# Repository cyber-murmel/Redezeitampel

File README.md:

# Redezeitampel
A traffic light like device to keep discussions calm and ordered

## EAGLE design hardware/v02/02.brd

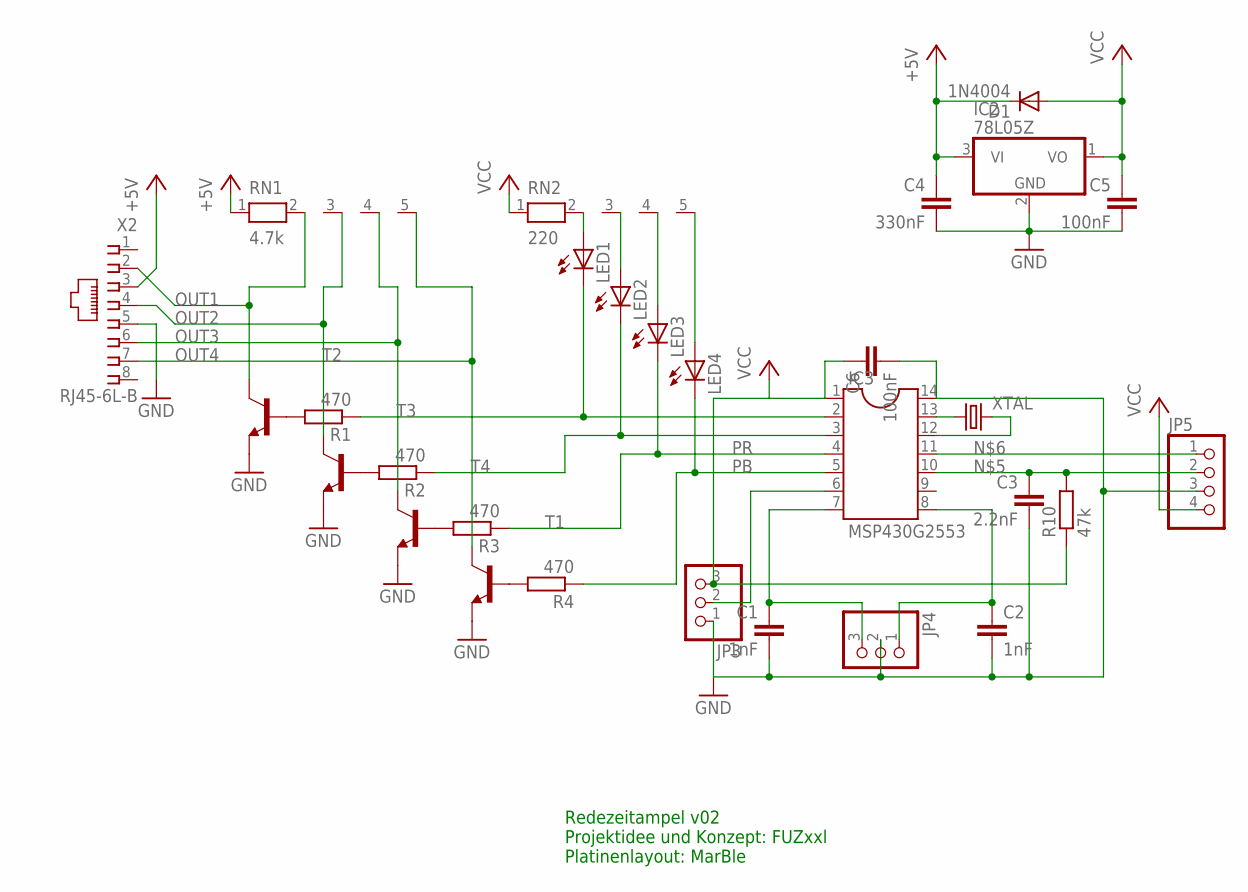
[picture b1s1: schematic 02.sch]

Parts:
C1, C2: 1nF; C025-024X044
C3: 2.2nF; C025-024X044
C4: 330nF; C050-024X044
C5, C6: 100nF; C050-024X044
D1: 1N4004; DO41-10
IC2: 78L05Z; TO92
IC3: MSP430G2553; SOCKET-14
JP3, JP4: PINHD-1X3; 1X03
JP5: PINHD-1X4; 1X04
LED1, LED2, LED3, LED4: LED5MM
R1, R2, R3, R4: 470; 0207/12
R10: 47k; 0207/7
RN1: 4.7k; RN-5
RN2: 220; RN-5
T1, T2, T3, T4: -NPN-TO92-EBC; TO92-EBC
X2: RJ45-6L-B; RJ45-NO-SHIELD
XTAL: CRYSTALTC26H; TC26H

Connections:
+5V: C4.1, D1.C, IC2.3 (VI), RN1.1, X2.3
GND: C1.2, C2.2, C3.2, C4.2, C5.2, C6.2, IC2.2 (GND), IC3.14, JP3.1, JP4.2, JP5.3, T1.E, T2.E, T3.E, T4.E, X2.5
unnamed: IC3.6, JP3.2
unnamed: IC3.13, XTAL.1
unnamed: C1.1, IC3.7, JP4.3
unnamed: C2.1, IC3.8, JP4.1
unnamed: C3.1, IC3.10, JP5.2, R10.2
unnamed: IC3.11, JP5.1
unnamed: IC3.12, XTAL.2
unnamed: LED1.A, RN2.2
unnamed: IC3.3, LED2.K (C), R2.1
unnamed: LED2.A, RN2.3
unnamed: R4.2, T1.B
unnamed: IC3.2, LED1.K (C), R1.1
unnamed: LED3.A, RN2.4
unnamed: LED4.A, RN2.5
unnamed: R1.2, T2.B
unnamed: R2.2, T3.B
unnamed: R3.2, T4.B
OUT1: RN1.2, T2.C, X2.2
OUT2: RN1.3, T3.C, X2.4
OUT3: RN1.4, T4.C, X2.6
OUT4: RN1.5, T1.C, X2.7
PB: IC3.5, LED4.K (C), R4.1
PR: IC3.4, LED3.K (C), R3.1
VCC: C5.1, C6.1, D1.A, IC2.1 (VO), IC3.1, JP3.3, JP5.4, R10.1, RN2.1

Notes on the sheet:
Redezeitampel v02 Projektidee und Konzept: FUZxxl Platinenlayout: MarBle

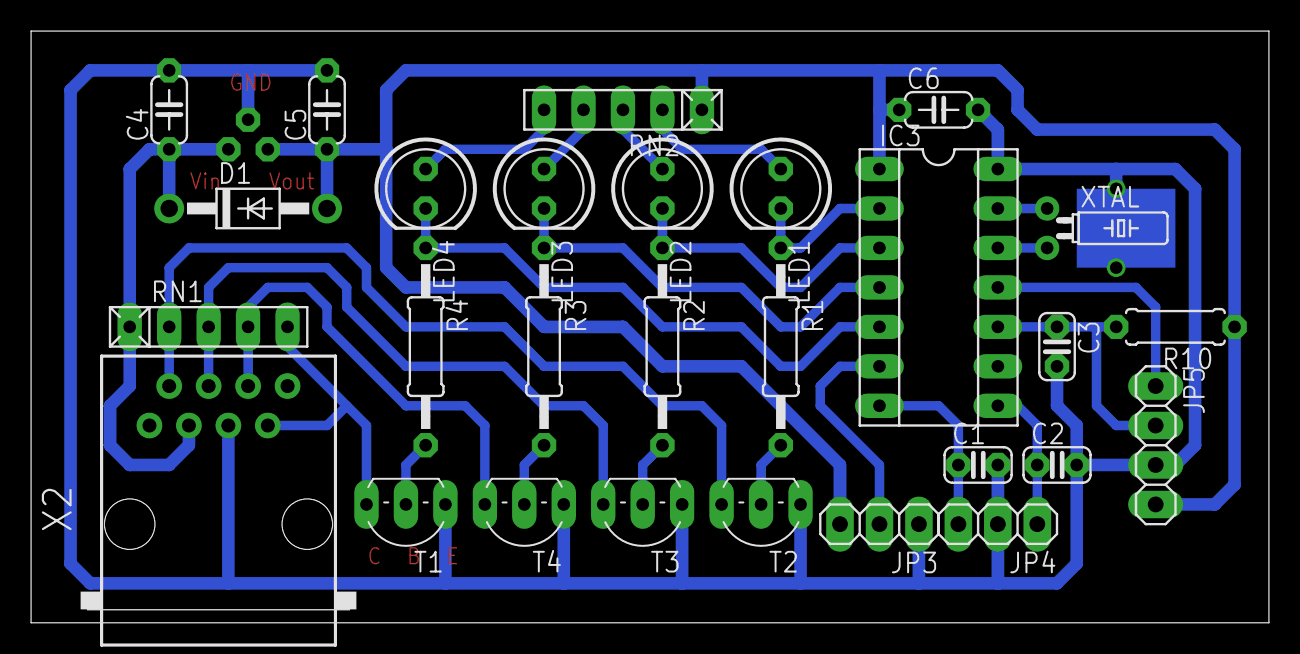
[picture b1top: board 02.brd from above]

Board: 2 copper layers, 79.7 x 38.1 mm, 29 parts (1 on the bottom side), 26 nets.

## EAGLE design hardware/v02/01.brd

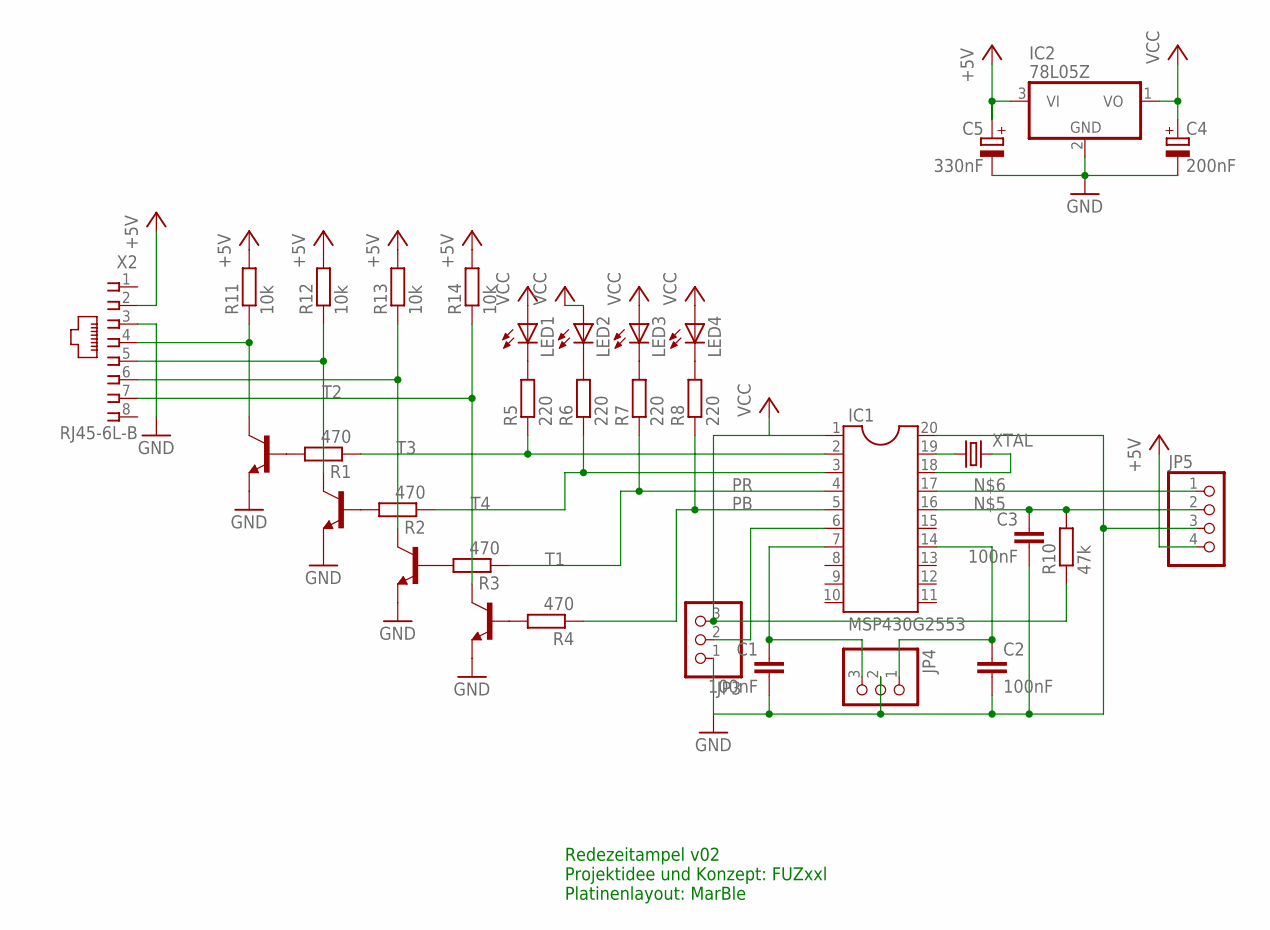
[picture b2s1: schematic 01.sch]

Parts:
C1, C2, C3: 100nF; C025-024X044
C4: 200nF; B45181A
C5: 330nF; B45181A
IC1: MSP430G2553; DIL20
IC2: 78L05Z; TO92
JP3, JP4: PINHD-1X3; 1X03
JP5: PINHD-1X4/90; 1X04/90
LED1, LED2, LED3, LED4: LED5MM
R1, R2, R3, R4: 470; 0207/10
R5, R6, R7, R8: 220; 0207/10
R10: 47k; 0207/10
R11, R12, R13, R14: 10k; 0207/10
T1, T2, T3, T4: -NPN-TO92-EBC; TO92-EBC
X2: RJ45-6L-B; RJ45-NO-SHIELD
XTAL: CRYSTALTC26H; TC26H

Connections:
+5V: C5.+, IC2.3 (VI), JP5.4, R11.2, R12.2, R13.2, R14.2, X2.2
GND: C1.2, C2.2, C3.2, C4.-, C5.-, IC1.20, IC2.2 (GND), JP3.1, JP4.2, JP5.3, T1.E, T2.E, T3.E, T4.E, X2.3
unnamed: IC1.6, JP3.2
unnamed: IC1.19, XTAL.1
unnamed: C1.1, IC1.7, JP4.3
unnamed: C2.1, IC1.14, JP4.1
unnamed: C3.1, IC1.16, JP5.2, R10.2
unnamed: IC1.17, JP5.1
unnamed: IC1.18, XTAL.2
unnamed: LED4.K (C), R8.2
unnamed: IC1.3, R2.1, R6.1
unnamed: R4.2, T1.B
unnamed: IC1.2, R1.1, R5.1
unnamed: LED1.K (C), R5.2
unnamed: R1.2, T2.B
unnamed: LED2.K (C), R6.2
unnamed: R2.2, T3.B
unnamed: LED3.K (C), R7.2
unnamed: R3.2, T4.B
unnamed: R14.1, T1.C, X2.7
unnamed: R13.1, T4.C, X2.6
unnamed: R12.1, T3.C, X2.5
unnamed: R11.1, T2.C, X2.4
PB: IC1.5, R4.1, R8.1
PR: IC1.4, R3.1, R7.1
VCC: C4.+, IC1.1, IC2.1 (VO), JP3.3, LED1.A, LED2.A, LED3.A, LED4.A, R10.1

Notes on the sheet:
Redezeitampel v02 Projektidee und Konzept: FUZxxl Platinenlayout: MarBle

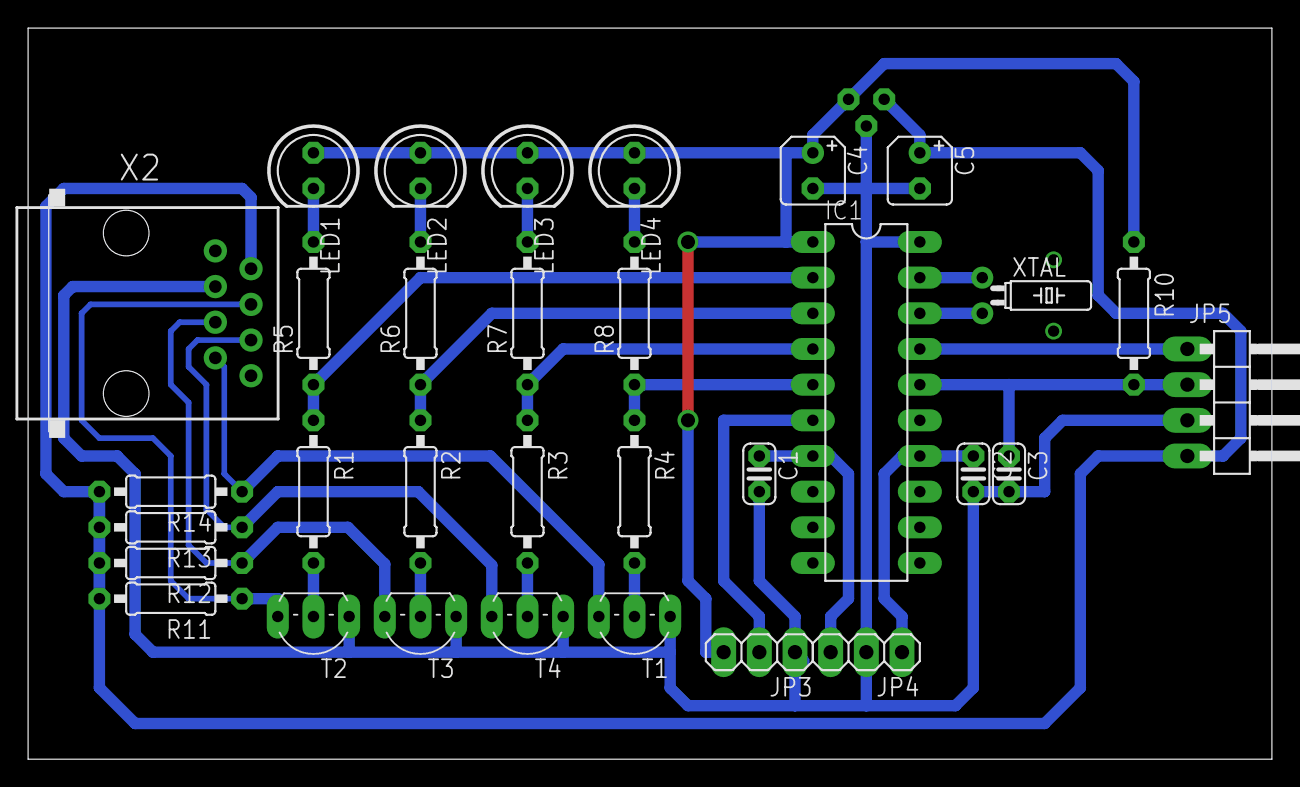
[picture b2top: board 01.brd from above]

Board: 2 copper layers, 88.6 x 52.0 mm, 33 parts (1 on the bottom side), 26 nets.

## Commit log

2015-10-06 Schaltplan der Steuerplatine
2015-10-06 kleine Korrekturen am Schaltplan
2015-10-08 mal gucken, was mit symlinks passiert
2015-10-08 deleted symlink
2015-10-08 Added eagle files
    old eagle files in v01
    at the moment v02 is copy of v01
2015-10-08 XTAl flat on board; holes for additional wire
2015-10-08 C3 between RST and GND
2015-10-08 C4 between Vcc and GND
2015-10-08 rearranged transistorsand LEDs; additional resistors; pre final version
2015-10-08 add pictures
2015-10-08 remove unneccesary files
2015-10-08 Reverting to the state of the project at 678c016824e7177dd6d43b6df3310d67c5eb1f45
2015-10-08 remove/rename some files
2015-10-09 avoid one wire bridge
2015-10-09 wire labels
2015-10-09 Layout der 4. Revision als Skizze
2015-10-09 Entwicklungszustand der Firmware
2015-10-09 winzige Korrektur des Schaltplans
2015-10-09 Besserer Dateiname für layout.jpg
2015-10-09 resistor networks, reposition Vreg
2015-10-09 images of newest version
2015-10-09 rearrange
2015-10-09 Datenblätter
2015-10-09 smaller IC; rearrange
2015-10-09 remove old files
2015-10-09 minor change
2015-10-09 denser distribution
2015-10-09 all caps converted to ceramic; diode over Vreg
2015-10-09 reposition XTAL
2015-10-09 minor changes
2015-10-09 add missing route
2015-10-10 echange pin header; labels on top
2015-10-10 CAM jobs for PCB top an bootom
2015-10-10 process plotte files
2015-10-12 reroute wires for optional mounting holes; XTAL GND plane
